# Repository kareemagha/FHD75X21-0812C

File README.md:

# FHD75X21-0812C
VFD driver for FHD75X21-0812C 

## Preview
Backside

Frontside

Demo

## Theory

The PT6315 IC is the brains of this driver. It is nothing more than some RAM and some shift registers. This IC uses SPI for communication, with the strobe, STB, pin acting as chip select (slave select). However, I would not reccomend using an SPI library to communicate with this IC, since the chip select functionality is non-standard.

The board contains an inverting boost converter. It generates -24V from a 5V input. This voltage is used for the filaments, grids and segments. Note that this voltage is just a reference/bias - nothing is driven from the -24V (put simply little current is drawn from the -24V source, a motor driver is used to pull current from the 5V input and a biasing circuit sets the voltage to -24V). A Schmitt trigger oscillator is used to simulate AC for the filament.

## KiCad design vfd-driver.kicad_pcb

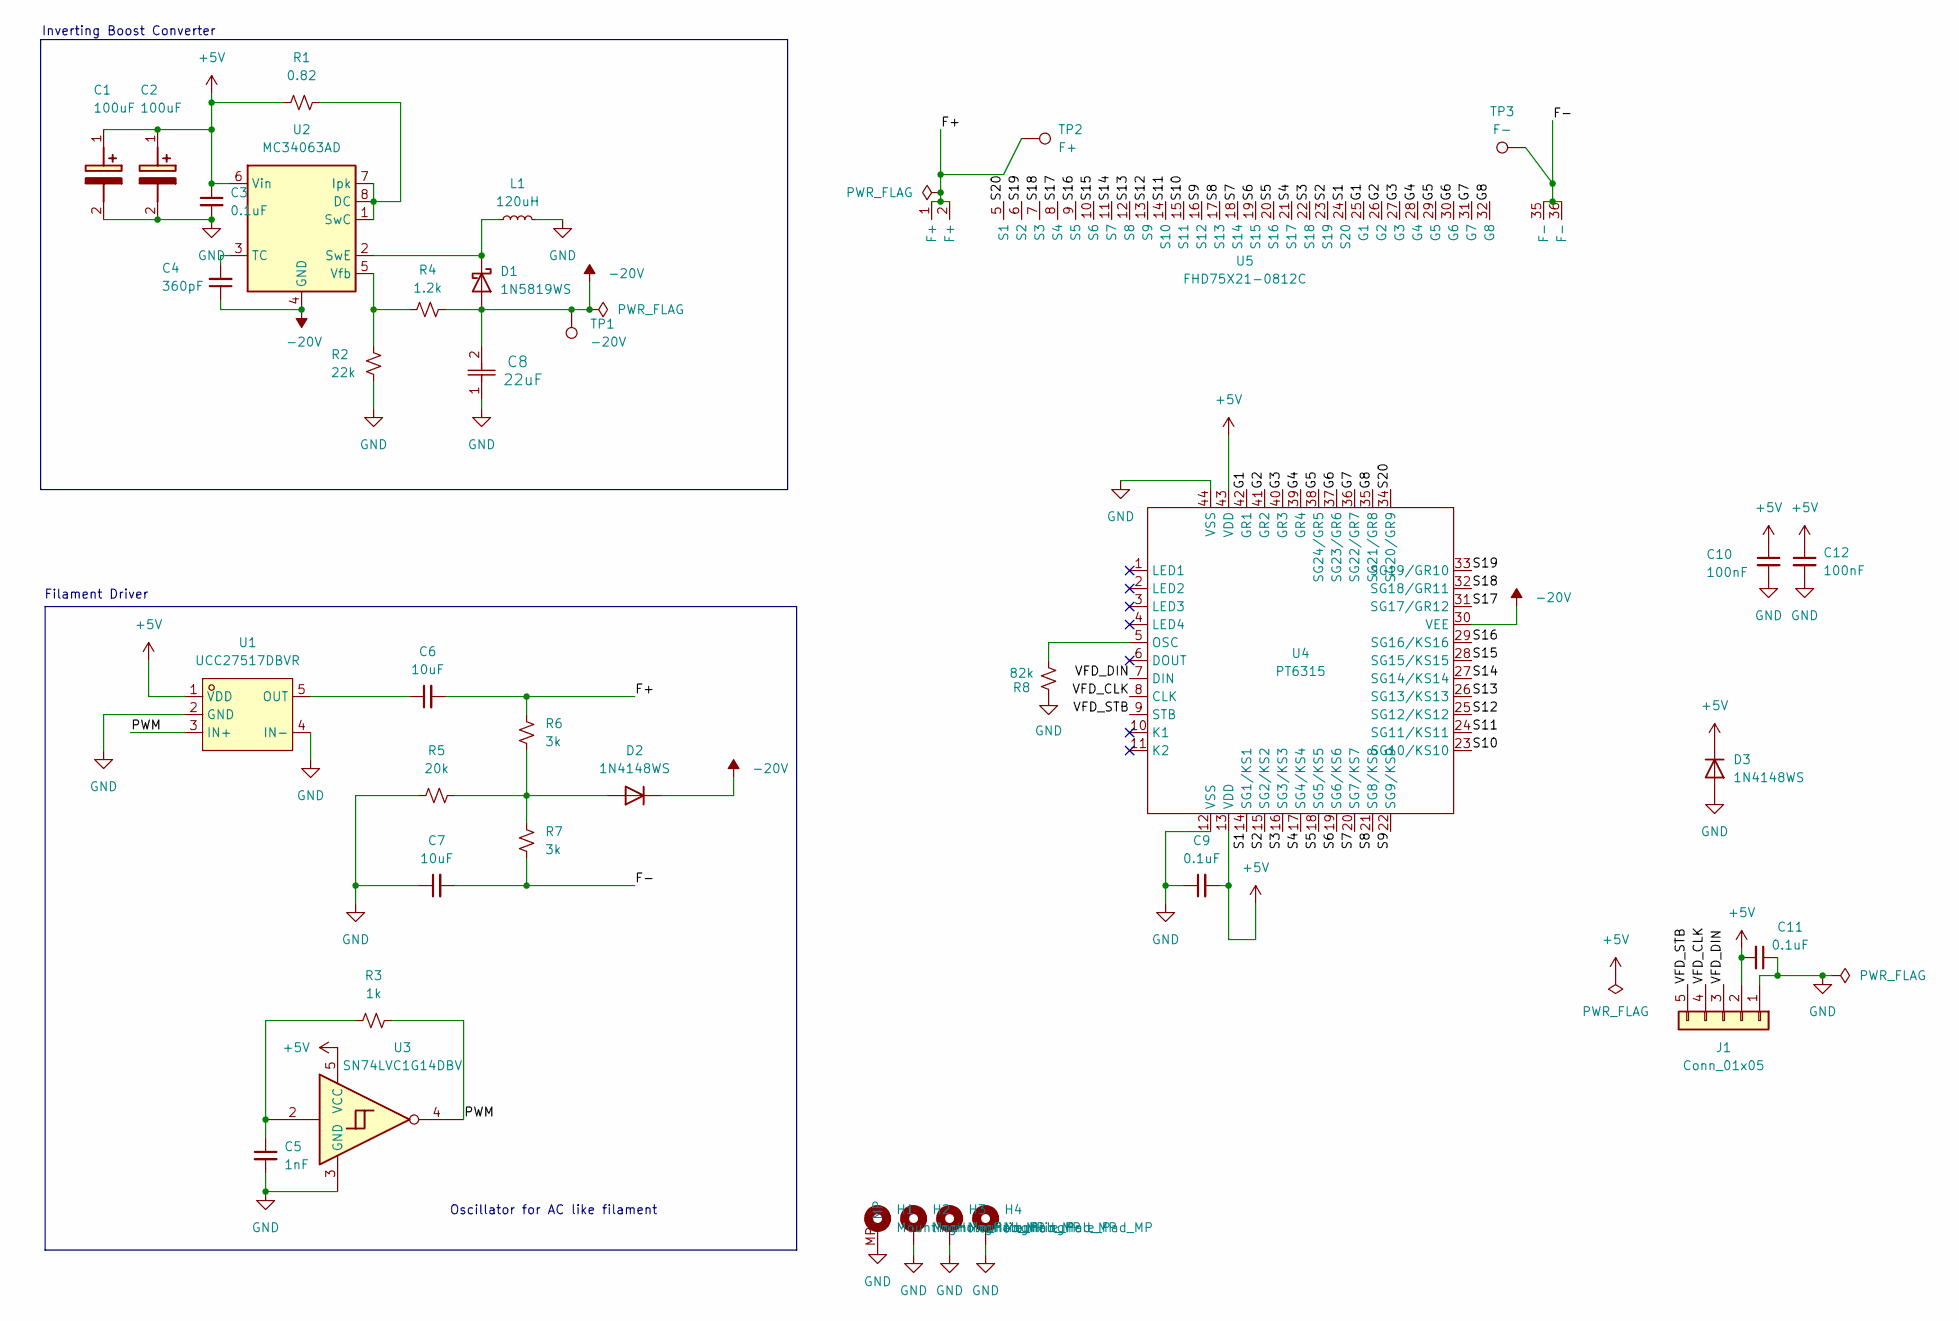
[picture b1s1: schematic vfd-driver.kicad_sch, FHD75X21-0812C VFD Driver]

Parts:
C1, C2: 100uF; CAPAE530X550N; Mouser Part Number 710-865080142007
C3, C11: 0.1uF; C_0603_1608Metric_Pad1.08x0.95mm_HandSolder
C4: 360pF; C_0805_2012Metric_Pad1.18x1.45mm_HandSolder
C5: 1nF; C_0603_1608Metric_Pad1.08x0.95mm_HandSolder; LCSC Part C100042
C6, C7: 10uF; C_0603_1608Metric_Pad1.08x0.95mm_HandSolder; LCSC Part C19702
C8: 22uF; CP_Elec_5x5.4
C9: 0.1uF; C_0603_1608Metric_Pad1.08x0.95mm_HandSolder; LCSC Part C14663
C10, C12: 100nF; C_0603_1608Metric_Pad1.08x0.95mm_HandSolder
D1: 1N5819WS; D_SOD-323F
D2, D3: 1N4148WS; D_SOD-323
H1, H2, H3, H4: MountingHole_Pad_MP; MountingHole_2.2mm_M2_Pad_Via
J1: Conn_01x05; PinSocket_1x05_P2.54mm_Vertical
L1: 120uH; L_Bourns_SRN6045TA
R1: 0.82; R_1206_3216Metric_Pad1.30x1.75mm_HandSolder
R2: 22k; R_0603_1608Metric_Pad0.98x0.95mm_HandSolder
R3: 1k; R_0603_1608Metric_Pad0.98x0.95mm_HandSolder; LCSC Part C22548
R4: 1.2k; R_0603_1608Metric_Pad0.98x0.95mm_HandSolder
R5: 20k; R_0603_1608Metric_Pad0.98x0.95mm_HandSolder; LCSC Part C2907011
R6, R7: 3k; R_0603_1608Metric_Pad0.98x0.95mm_HandSolder; LCSC Part C2907033
R8: 82k; R_0603_1608Metric_Pad0.98x0.95mm_HandSolder; LCSC Part C14675
TP1: -20V; TestPoint_Pad_1.0x1.0mm
TP2: F+; TestPoint_Pad_1.0x1.0mm
TP3: F-; TestPoint_Pad_1.0x1.0mm
U1: UCC27517DBVR; SOT-23-5_L3.0-W1.7-P0.95-LS2.8-BR; MPN UCC27517DBVR(UMW); LCSC Part C20623191
U2: MC34063AD; SOIC-8_3.9x4.9mm_P1.27mm
U3: SN74LVC1G14DBV; SOT-23-5
U4: PT6315; LQFP-44_10x10mm_P0.8mm
U5: FHD75X21-0812C; PinSocket_1x36_P1.875mm_Vertical

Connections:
+5V: C1.1 (+), C2.1 (+), C3.1, C9.2, C10.1, C11.2, C12.1, D3.1 (K), J1.2, R1.1, U1.1 (VDD), U2.6 (Vin), U3.5 (VCC), U4.13 (VDD), U4.43 (VDD)
-20V: C4.1, C8.2, D1.2 (A), D2.1 (K), R4.2, TP1.1 (1_1), U2.4 (GND), U4.30 (VEE)
/F+: C6.2, R6.2, TP2.1 (1_1), U5.1 (F+), U5.2 (F+)
/F-: C7.2, R7.1, TP3.1 (1_1), U5.35 (F-), U5.36 (F-)
/G1: U4.42 (GR1), U5.25 (G1)
/G2: U4.41 (GR2), U5.26 (G2)
/G3: U4.40 (GR3), U5.27 (G3)
/G4: U4.39 (GR4), U5.28 (G4)
/G5: U4.38 (SG24/GR5), U5.29 (G5)
/G6: U4.37 (SG23/GR6), U5.30 (G6)
/G7: U4.36 (SG22/GR7), U5.31 (G7)
/G8: U4.35 (SG21/GR8), U5.32 (G8)
/PWM: R3.2, U1.3 (IN+), U3.4
/S1: U4.14 (SG1/KS1), U5.24 (S20)
/S2: U4.15 (SG2/KS2), U5.23 (S19)
/S3: U4.16 (SG3/KS3), U5.22 (S18)
/S4: U4.17 (SG4/KS4), U5.21 (S17)
/S5: U4.18 (SG5/KS5), U5.20 (S16)
/S6: U4.19 (SG6/KS6), U5.19 (S15)
/S7: U4.20 (SG7/KS7), U5.18 (S14)
/S8: U4.21 (SG8/KS8), U5.17 (S13)
/S9: U4.22 (SG9/KS9), U5.16 (S12)
/S10: U4.23 (SG10/KS10), U5.15 (S11)
/S11: U4.24 (SG11/KS11), U5.14 (S10)
/S12: U4.25 (SG12/KS12), U5.13 (S9)
/S13: U4.26 (SG13/KS13), U5.12 (S8)
/S14: U4.27 (SG14/KS14), U5.11 (S7)
/S15: U4.28 (SG15/KS15), U5.10 (S6)
/S16: U4.29 (SG16/KS16), U5.9 (S5)
/S17: U4.31 (SG17/GR12), U5.8 (S4)
/S18: U4.32 (SG18/GR11), U5.7 (S3)
/S19: U4.33 (SG19/GR10), U5.6 (S2)
/S20: U4.34 (SG20/GR9), U5.5 (S1)
/VFD_CLK: J1.4, U4.8 (CLK)
/VFD_DIN: J1.3, U4.7 (DIN)
/VFD_STB: J1.5, U4.9 (STB)
GND: C1.2 (-), C2.2 (-), C3.2, C5.2, C7.1, C8.1, C9.1, C10.2, C11.1, C12.2, D3.2 (A), H1.1, H1.MP, H2.1, H2.MP, H3.1, H3.MP, H4.1, H4.MP, J1.1, L1.2, R2.2, R5.1, R8.1, U1.2 (GND), U1.4 (IN-), U3.3 (GND), U4.12 (VSS), U4.44 (VSS)
unnamed: C5.1, R3.1, U3.2
unnamed: D1.1 (K), L1.1, U2.2 (SwE)
unnamed: D2.2 (A), R5.2, R6.1, R7.2
unnamed: C6.1, U1.5 (OUT)
unnamed: R1.2, U2.1 (SwC), U2.7 (Ipk), U2.8 (DC)
unnamed: C4.2, U2.3 (TC)
unnamed: R2.1, R4.1, U2.5 (Vfb)
unnamed: R8.2, U4.5 (OSC)

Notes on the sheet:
Oscillator for AC like filament
Filament Driver
Inverting Boost Converter

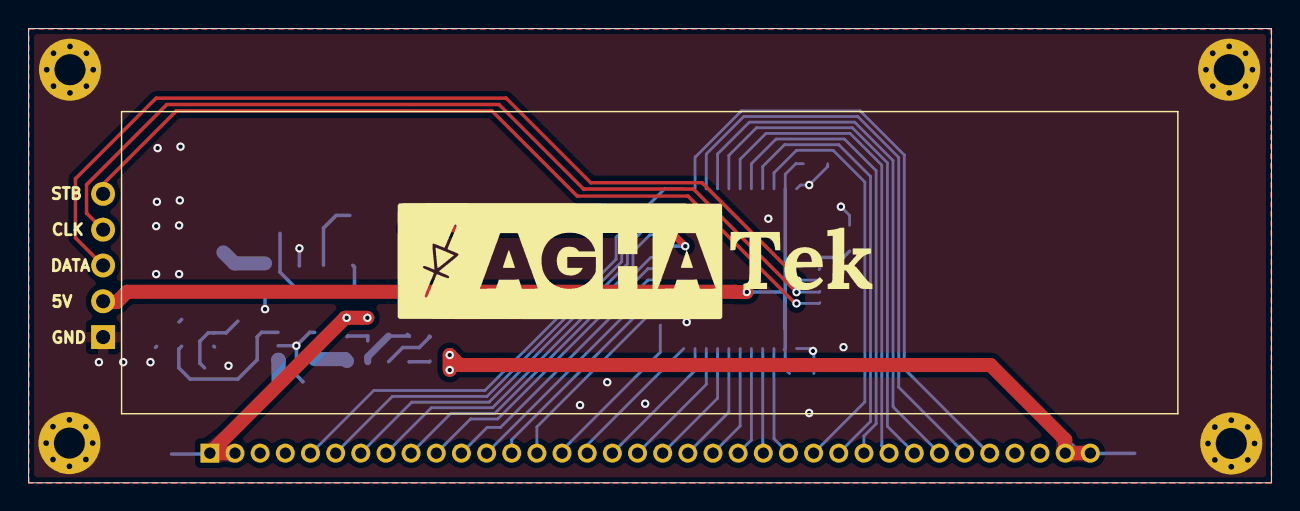
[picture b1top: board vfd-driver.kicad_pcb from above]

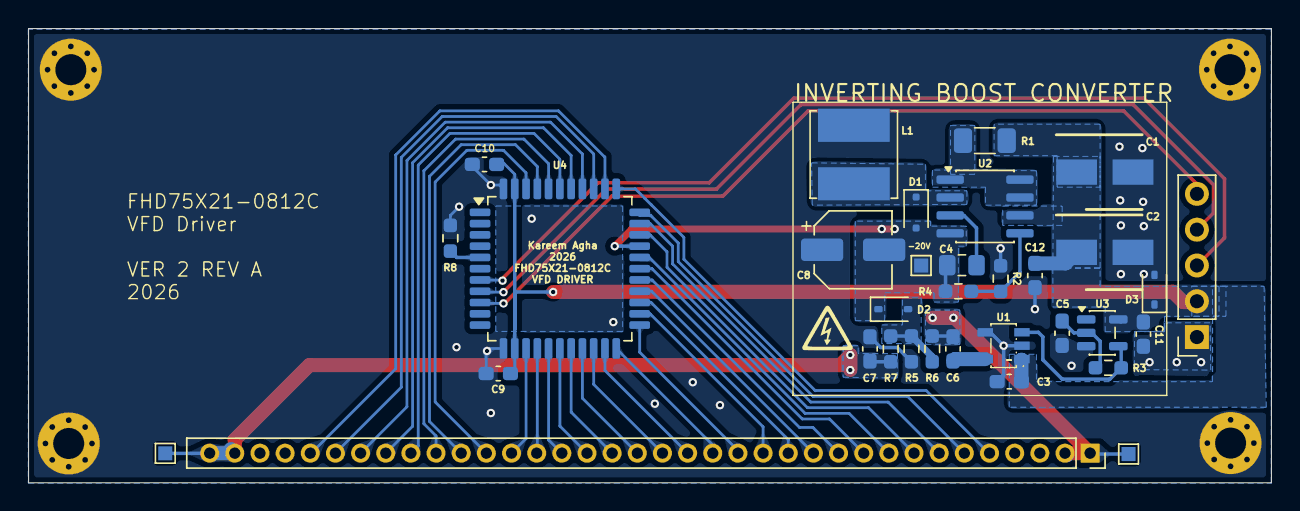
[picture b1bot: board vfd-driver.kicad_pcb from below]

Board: 2 copper layers, 88.2 x 32.2 mm, 37 parts (33 on the bottom side), 45 nets.
